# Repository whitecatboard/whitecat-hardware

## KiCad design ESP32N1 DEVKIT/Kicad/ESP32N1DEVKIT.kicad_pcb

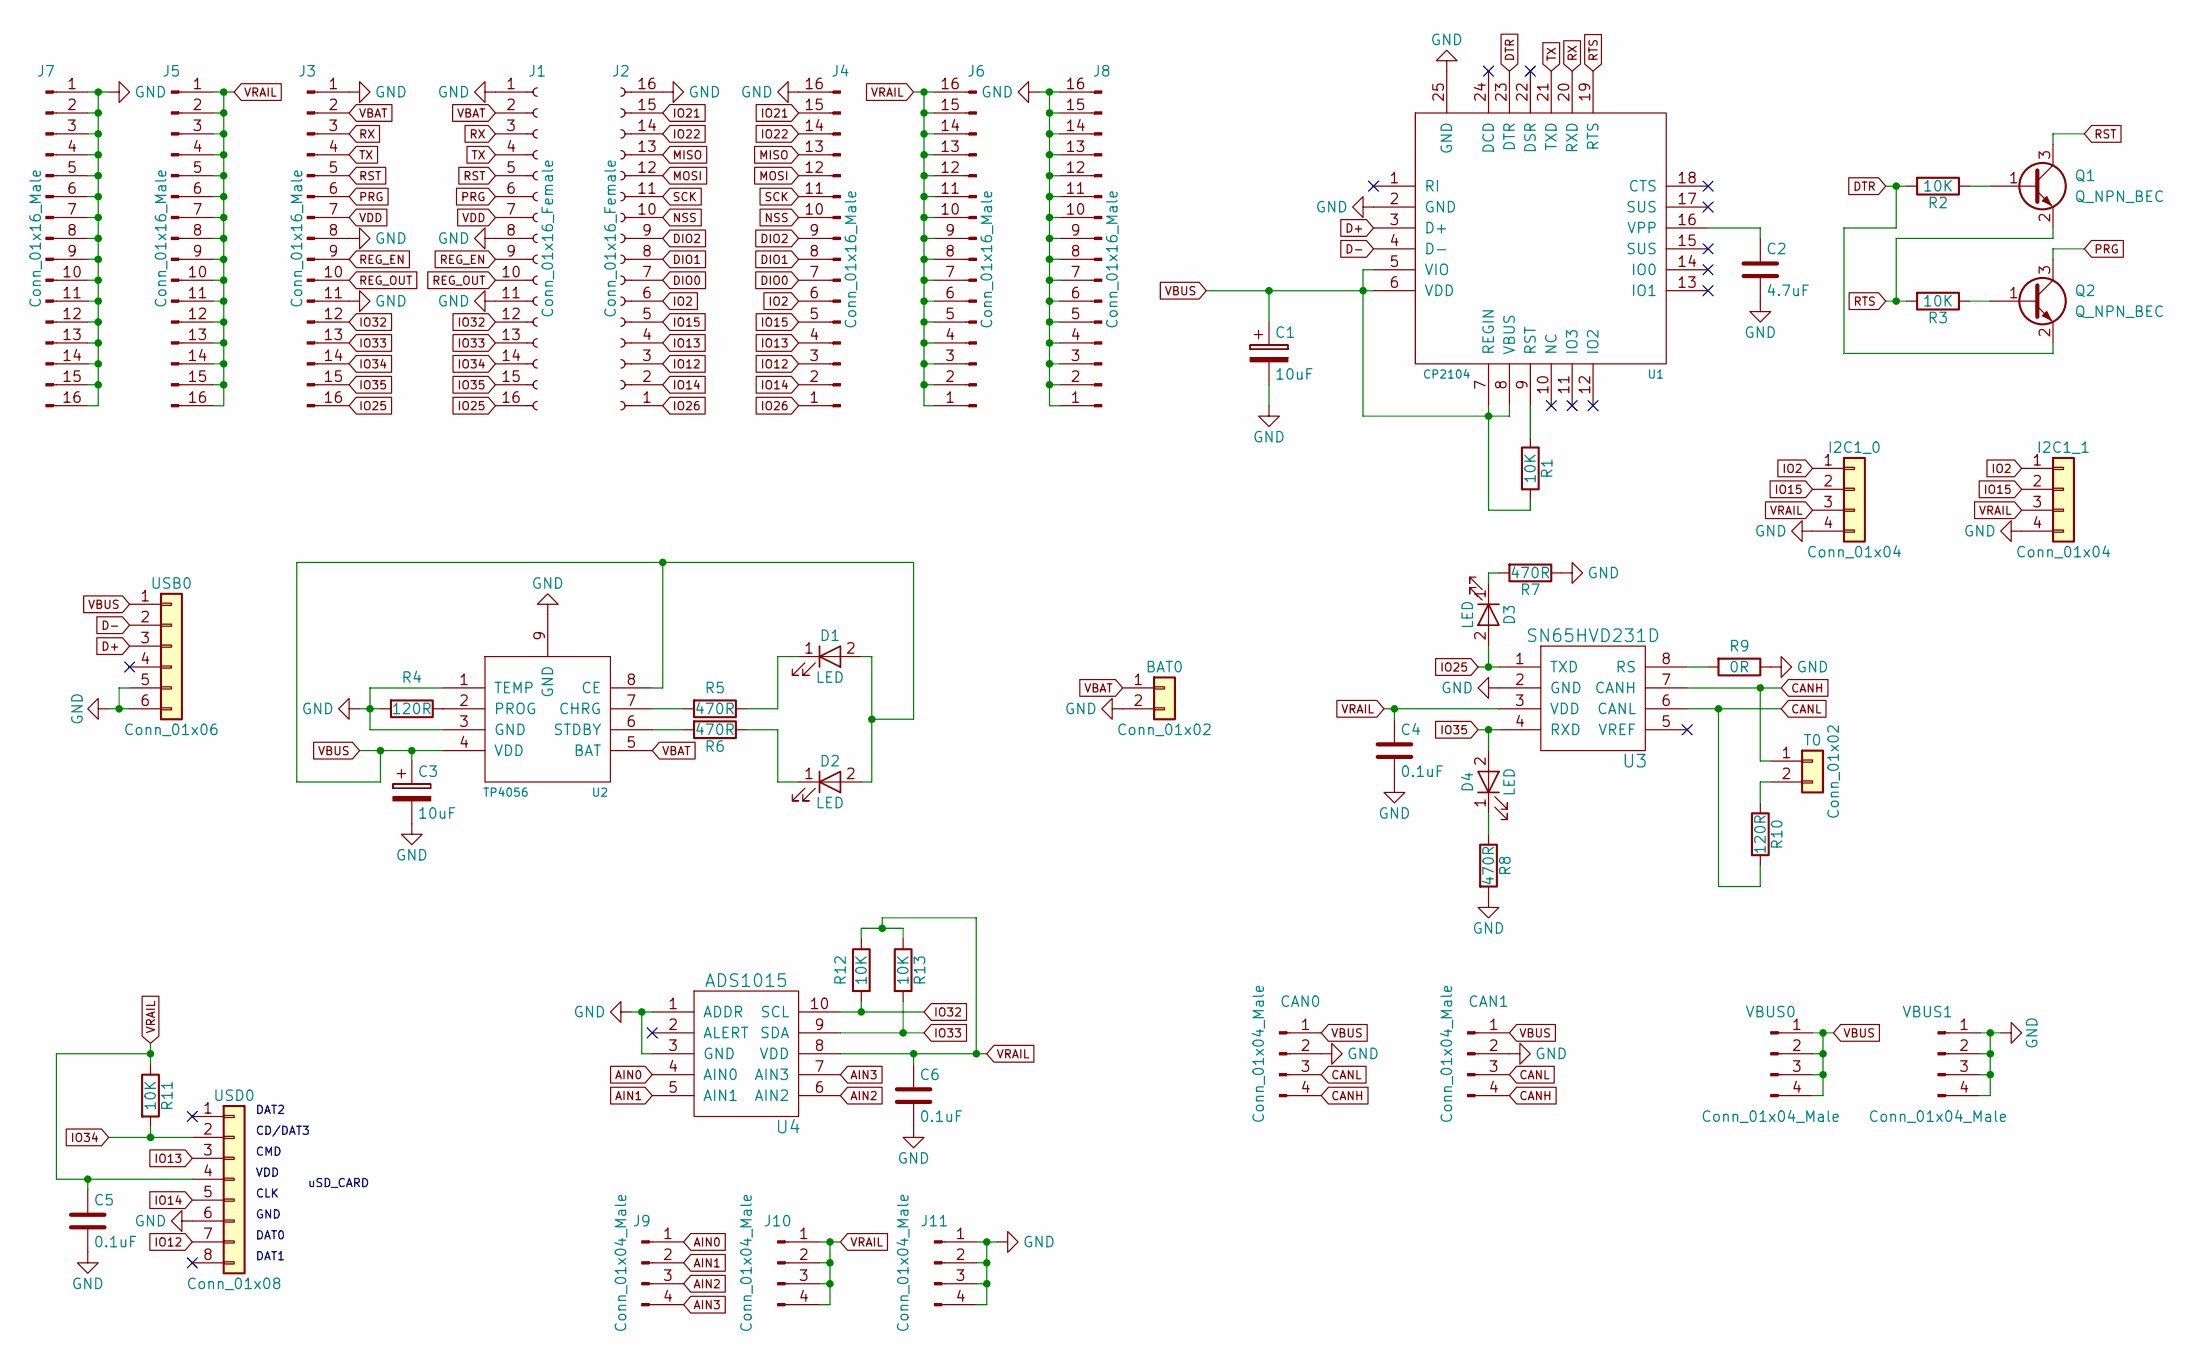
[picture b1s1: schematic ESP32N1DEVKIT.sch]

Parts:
BAT0: Conn_01x02; 18650_holder
C1, C3: 10uF; CP_Tantalum_Case-A_EIA-3216-18_Reflow
C2: 4.7uF; C_0603
C4, C5, C6: 0.1uF; C_0603
CAN0, CAN1: Conn_01x04_Male; micro_match_4p
D1, D2, D3, D4: LED; LED_0603
I2C1_0, I2C1_1: Conn_01x04; Pin_Header_Straight_1x04_Pitch2.54mm
J1, J2: Conn_01x16_Female; Pin_Header_Straight_1x16_Pitch2.54mm
J3, J4, J5, J6, J7, J8: Conn_01x16_Male; Pin_Header_Straight_1x16_Pitch2.54mm
J9, J10, J11: Conn_01x04_Male; Pin_Header_Straight_1x04_Pitch2.54mm
Q1, Q2: Q_NPN_BEC; SOT-23
R1, R2, R3, R11, R12, R13: 10K; R_0603
R4, R10: 120R; R_0603
R5, R6, R7, R8: 470R; R_0603
R9: 0R; R_0603
T0: Conn_01x02; Pin_Header_Straight_1x02_Pitch2.54mm
U1: CP2104; QFN-24-1EP_4x4mm_Pitch0.5mm
U2: TP4056; SOIC-8-1EP_3.9x4.9mm_Pitch1.27mm
U3: SN65HVD231D; SOIC-8_3.9x4.9mm_Pitch1.27mm
U4: ADS1015; TSSOP-10_3x3mm_Pitch0.5mm
USB0: Conn_01x06; USB_Mini-B
USD0: Conn_01x08; msd_socket
VBUS0, VBUS1: Conn_01x04_Male; Pin_Header_Straight_1x04_Pitch2.54mm

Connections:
AIN0: J9.1, U4.4 (AIN0)
AIN1: J9.2, U4.5 (AIN1)
AIN2: J9.3, U4.6 (AIN2)
AIN3: J9.4, U4.7 (AIN3)
CANH: CAN0.4, CAN1.4, T0.1, U3.7 (CANH)
CANL: CAN0.3, CAN1.3, R10.2, U3.6 (CANL)
D+: U1.3 (D+), USB0.3
D-: U1.4 (D-), USB0.2
DIO0: J2.7, J4.7
DIO1: J2.8, J4.8
DIO2: J2.9, J4.9
DTR: Q2.2 (E), R2.2, U1.23 (DTR)
GND: BAT0.2, C1.2, C2.2, C3.2, C4.2, C5.2, C6.2, CAN0.2, CAN1.2, I2C1_0.4, I2C1_1.4, J1.1, J1.8, J1.11, J2.16, J3.1, J3.8, J3.11, J4.16, J7.1, J7.2, J7.3, J7.4, J7.5, J7.6, J7.7, J7.8, J7.9, J7.10, J7.11, J7.12, J7.13, J7.14, J7.15, J7.16, J8.1, J8.2, J8.3, J8.4, J8.5, J8.6, J8.7, J8.8, J8.9, J8.10, J8.11, J8.12, J8.13, J8.14, J8.15, J8.16, J11.1, J11.2, J11.3, J11.4, R4.2, R7.1, R8.2, R9.1, U1.2 (GND), U1.25 (GND), U2.1 (TEMP), U2.3 (GND), U2.9 (GND), U3.2 (GND), U4.1 (ADDR), U4.3 (GND), USB0.5, USB0.6, USD0.6, VBUS1.1, VBUS1.2, VBUS1.3, VBUS1.4
IO2: I2C1_0.1, I2C1_1.1, J2.6, J4.6
IO12: J2.3, J4.3, USD0.7
IO13: J2.4, J4.4, USD0.3
IO14: J2.2, J4.2, USD0.5
IO15: I2C1_0.2, I2C1_1.2, J2.5, J4.5
IO21: J2.15, J4.15
IO22: J2.14, J4.14
IO25: D3.2 (A), J1.16, J3.16, U3.1 (TXD)
IO26: J2.1, J4.1
IO32: J1.12, J3.12, R12.2, U4.10 (SCL)
IO33: J1.13, J3.13, R13.2, U4.9 (SDA)
IO34: J1.14, J3.14, R11.2, USD0.2
IO35: D4.2 (A), J1.15, J3.15, U3.4 (RXD)
MISO: J2.13, J4.13
MOSI: J2.12, J4.12
NSS: J2.10, J4.10
unnamed: C2.1, U1.16 (VPP)
unnamed: D1.1 (K), R5.1
unnamed: D2.1 (K), R6.1
unnamed: D3.1 (K), R7.2
unnamed: D4.1 (K), R8.1
unnamed: Q1.1 (B), R2.1
unnamed: Q2.1 (B), R3.1
unnamed: R1.1, U1.9 (RST)
unnamed: R4.1, U2.2 (PROG)
unnamed: R5.2, U2.7 (CHRG)
unnamed: R6.2, U2.6 (STDBY)
unnamed: R9.2, U3.8 (RS)
unnamed: R10.1, T0.2
PRG: J1.6, J3.6, Q2.3 (C)
REG_EN: J1.9, J3.9
REG_OUT: J1.10, J3.10
RST: J1.5, J3.5, Q1.3 (C)
RTS: Q1.2 (E), R3.2, U1.19 (RTS)
RX: J1.3, J3.3, U1.20 (RXD)
SCK: J2.11, J4.11
TX: J1.4, J3.4, U1.21 (TXD)
VBAT: BAT0.1, J1.2, J3.2, U2.5 (BAT)
VBUS: C1.1, C3.1, CAN0.1, CAN1.1, D1.2 (A), D2.2 (A), R1.2, U1.5 (VIO), U1.6 (VDD), U1.7 (REGIN), U1.8 (VBUS), U2.4 (VDD), U2.8 (CE), USB0.1, VBUS0.1, VBUS0.2, VBUS0.3, VBUS0.4
VDD: J1.7, J3.7
VRAIL: C4.1, C5.1, C6.1, I2C1_0.3, I2C1_1.3, J5.1, J5.2, J5.3, J5.4, J5.5, J5.6, J5.7, J5.8, J5.9, J5.10, J5.11, J5.12, J5.13, J5.14, J5.15, J5.16, J6.1, J6.2, J6.3, J6.4, J6.5, J6.6, J6.7, J6.8, J6.9, J6.10, J6.11, J6.12, J6.13, J6.14, J6.15, J6.16, J10.1, J10.2, J10.3, J10.4, R11.1, R12.1, R13.1, U3.3 (VDD), U4.8 (VDD), USD0.4

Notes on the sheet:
DAT2
CD/DAT3
CMD
VDD
CLK
GND
DAT0
DAT1
uSD_CARD

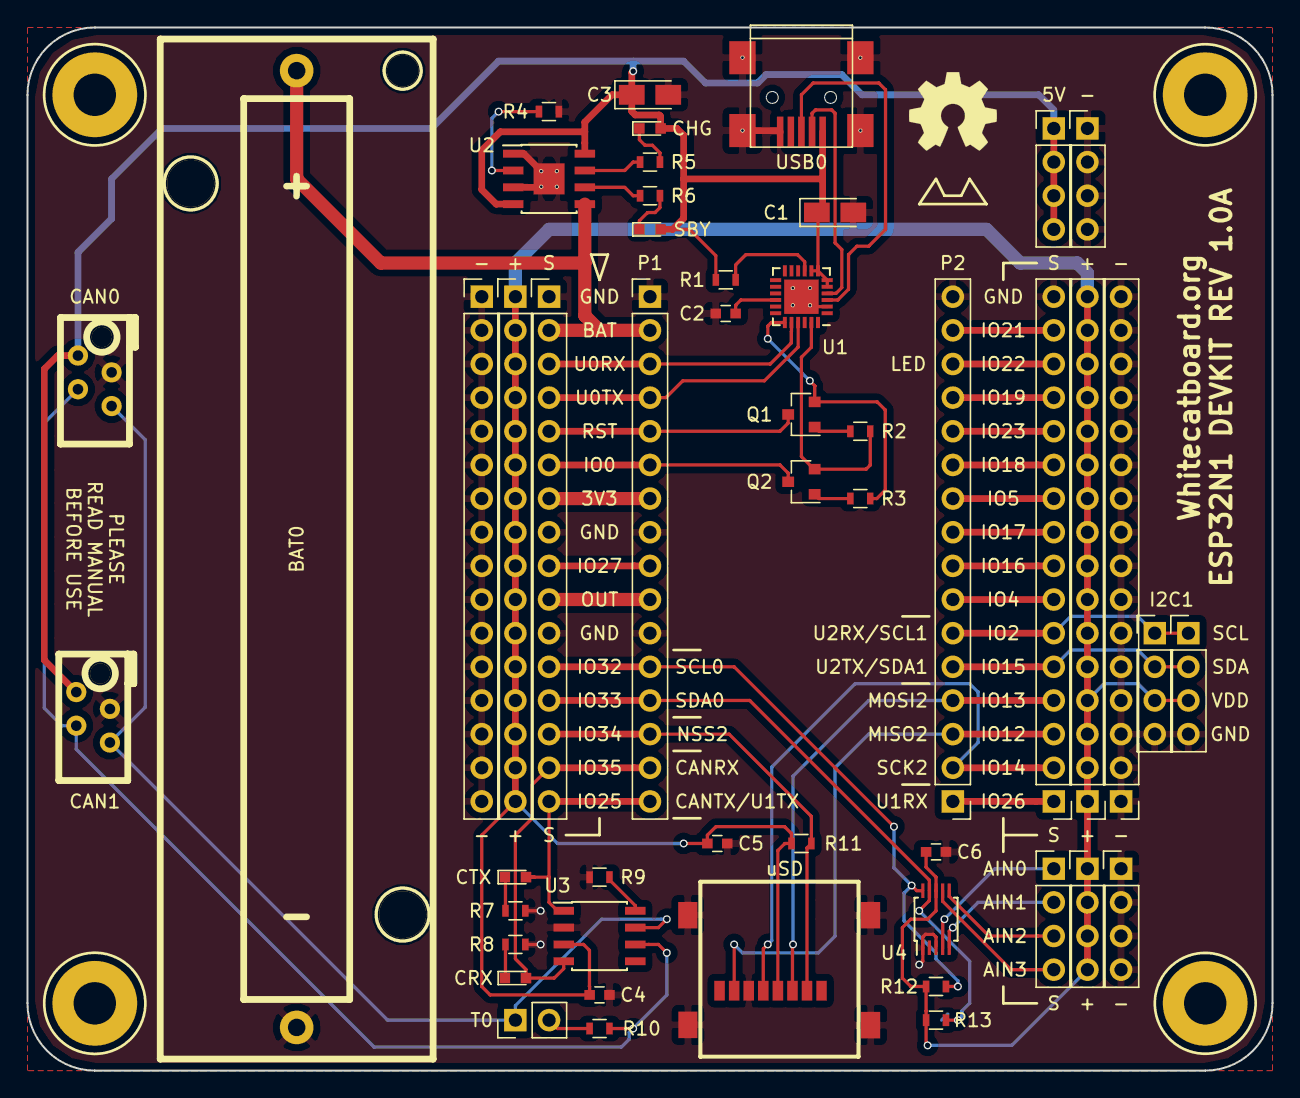
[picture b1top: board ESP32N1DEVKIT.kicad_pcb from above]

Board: 2 copper layers, 94.0 x 78.7 mm, 50 parts (0 on the bottom side), 54 nets.

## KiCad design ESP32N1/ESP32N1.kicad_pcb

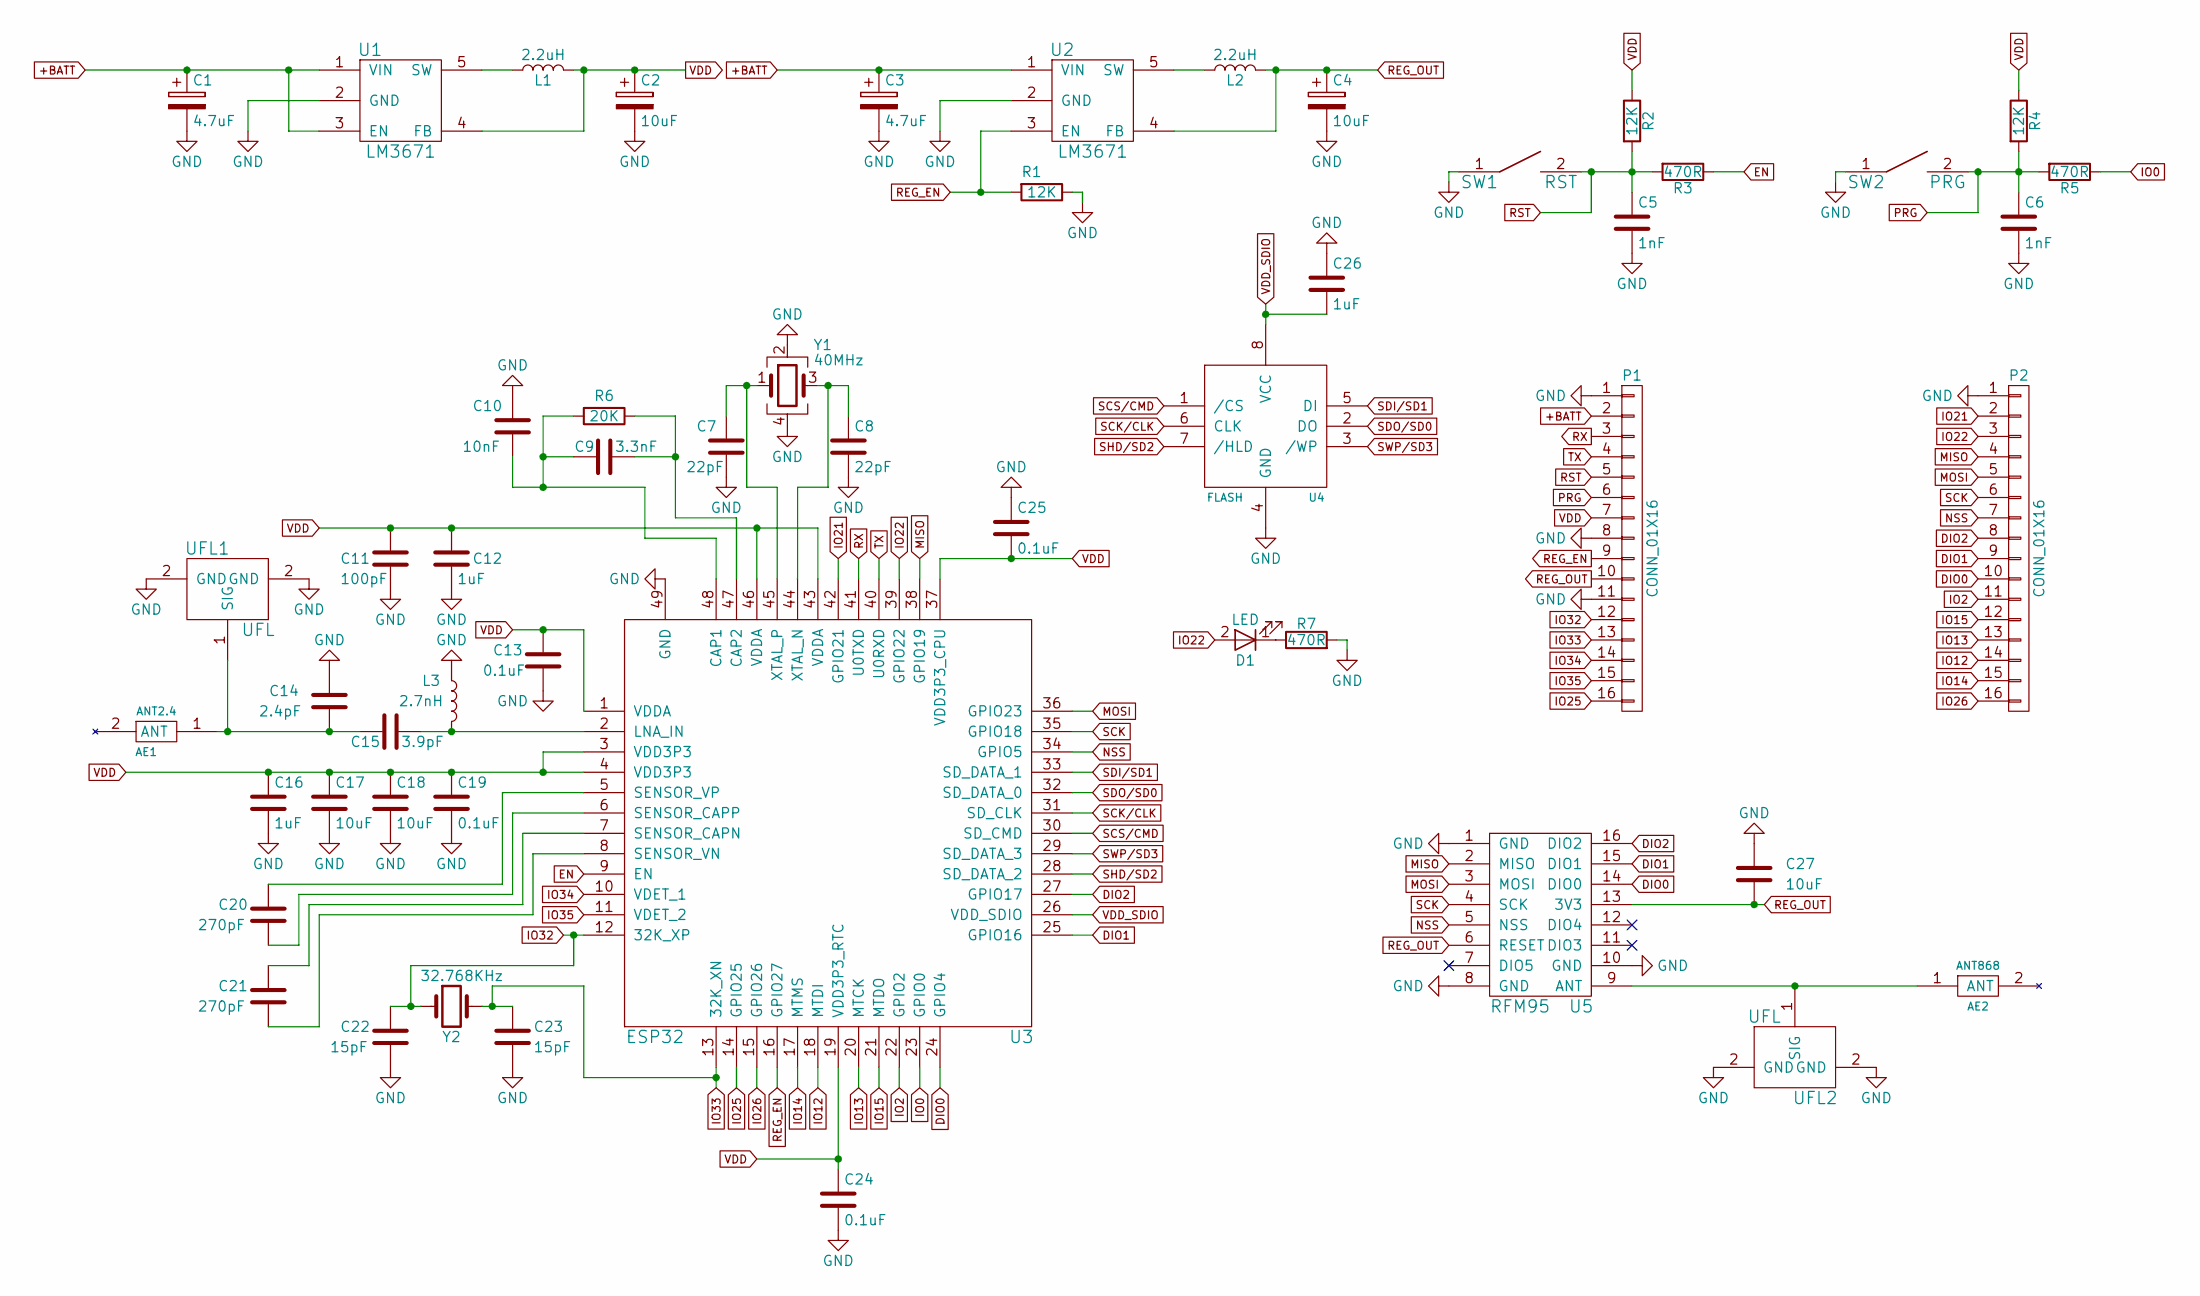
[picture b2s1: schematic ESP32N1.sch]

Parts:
AE1: ANT2.4
AE2: ANT868
C1, C3: 4.7uF; CP_Tantalum_Case-A_EIA-3216-18_Reflow
C2, C4: 10uF; CP_Tantalum_Case-A_EIA-3216-18_Reflow
C5, C6: 1nF; C_0603
C7, C8: 22pF; C_0603
C9: 3.3nF; C_0603
C10: 10nF; C_0603
C11: 100pF; C_0603
C12, C16, C26: 1uF; C_0603
C13, C19, C24, C25: 0.1uF; C_0603
C14: 2.4pF; C_0603
C15: 3.9pF; C_0603
C17, C18, C27: 10uF; C_0603
C20, C21: 270pF; C_0603
C22, C23: 15pF; C_0603
D1: LED; LED_0603
L1, L2: 2.2uH; R_0603
L3: 2.7nH; R_0603
P1, P2: CONN_01X16; Pin_Header_Straight_1x16_Pitch2.54mm
R1, R2, R4: 12K; R_0603
R3, R5, R7: 470R; R_0603
R6: 20K; R_0603
SW1: RST; PTS820
SW2: PRG; PTS820
U1, U2: LM3671; SOT-23-5
U3: ESP32; UQFN-48-1EP_6x6mm_Pitch0.4mm
U4: FLASH; SOIC-8-208
U5: RFM95; RFM95W
UFL1, UFL2: UFL; COAXIAL_U.FL-R-SMT-1
Y1: 40MHz; Crystal_SMD_TXC_7M-4pin_3.2x2.5mm
Y2: 32.768KHz; Crystal_SMD_MicroCrystal_CC7V-T1A-2pin_3.2x1.5mm

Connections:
+BATT: C1.1, C3.1, P1.2, U1.1 (VIN), U1.3 (EN), U2.1 (VIN)
DIO0: P2.10, U3.24 (GPIO4), U5.14 (DIO0)
DIO1: P2.9, U3.25 (GPIO16), U5.15 (DIO1)
DIO2: P2.8, U3.27 (GPIO17), U5.16 (DIO2)
EN: R3.1, U3.9 (EN)
GND: C1.2, C2.2, C3.2, C4.2, C5.2, C6.2, C7.2, C8.2, C10.1, C11.2, C12.2, C13.2, C14.1, C16.2, C17.2, C18.2, C19.2, C22.2, C23.2, C24.2, C25.1, C26.1, C27.1, L3.1, P1.1, P1.8, P1.11, P2.1, R1.1, R7.2, SW1.1, SW2.1, U1.2 (GND), U2.2 (GND), U3.49 (GND), U4.4 (GND), U5.1 (GND), U5.8 (GND), U5.10 (GND), UFL1.2 (GND), UFL2.2 (GND), Y1.2, Y1.4
IO0: R5.1, U3.23 (GPIO0)
IO2: P2.11, U3.22 (GPIO2)
IO12: P2.14, U3.18 (MTDI)
IO13: P2.13, U3.20 (MTCK)
IO14: P2.15, U3.17 (MTMS)
IO15: P2.12, U3.21 (MTDO)
IO21: P2.2, U3.42 (GPIO21)
IO22: D1.2 (A), P2.3, U3.39 (GPIO22)
IO25: P1.16, U3.14 (GPIO25)
IO26: P2.16, U3.15 (GPIO26)
IO32: C22.1, P1.12, U3.12 (32K_XP), Y2.1
IO33: C23.1, P1.13, U3.13 (32K_XN), Y2.2
IO34: P1.14, U3.10 (VDET_1)
IO35: P1.15, U3.11 (VDET_2)
MISO: P2.4, U3.38 (GPIO19), U5.2 (MISO)
MOSI: P2.5, U3.36 (GPIO23), U5.3 (MOSI)
NSS: P2.7, U3.34 (GPIO5), U5.5 (NSS)
unnamed: AE1.1 (ANT), C14.2, C15.2, UFL1.1 (SIG)
unnamed: AE2.1 (ANT), U5.9 (ANT), UFL2.1 (SIG)
unnamed: C7.1, U3.45 (XTAL_P), Y1.1
unnamed: C8.1, U3.44 (XTAL_N), Y1.3
unnamed: C9.1, R6.1, U3.47 (CAP2)
unnamed: C9.2, C10.2, R6.2, U3.48 (CAP1)
unnamed: C15.1, L3.2, U3.2 (LNA_IN)
unnamed: C20.1, U3.5 (SENSOR_VP)
unnamed: C20.2, U3.6 (SENSOR_CAPP)
unnamed: C21.1, U3.7 (SENSOR_CAPN)
unnamed: C21.2, U3.8 (SENSOR_VN)
unnamed: D1.1 (K), R7.1
unnamed: L1.1, U1.5 (SW)
unnamed: L2.1, U2.5 (SW)
PRG: C6.1, P1.6, R4.2, R5.2, SW2.2
REG_EN: P1.9, R1.2, U2.3 (EN), U3.16 (GPIO27)
REG_OUT: C4.1, C27.2, L2.2, P1.10, U2.4 (FB), U5.6 (RESET), U5.13 (3V3)
RST: C5.1, P1.5, R2.2, R3.2, SW1.2
RX: P1.3, U3.41 (U0TXD)
SCK: P2.6, U3.35 (GPIO18), U5.4 (SCK)
SCK/CLK: U3.31 (SD_CLK), U4.6 (CLK)
SCS/CMD: U3.30 (SD_CMD), U4.1 (/CS)
SDI/SD1: U3.33 (SD_DATA_1), U4.5 (DI)
SDO/SD0: U3.32 (SD_DATA_0), U4.2 (DO)
SHD/SD2: U3.28 (SD_DATA_2), U4.7 (/HLD)
SWP/SD3: U3.29 (SD_DATA_3), U4.3 (/WP)
TX: P1.4, U3.40 (U0RXD)
VDD: C2.1, C11.1, C12.1, C13.1, C16.1, C17.1, C18.1, C19.1, C24.1, C25.2, L1.2, P1.7, R2.1, R4.1, U1.4 (FB), U3.1 (VDDA), U3.3 (VDD3P3), U3.4 (VDD3P3), U3.19 (VDD3P3_RTC), U3.37 (VDD3P3_CPU), U3.43 (VDDA), U3.46 (VDDA)
VDD_SDIO: C26.2, U3.26 (VDD_SDIO), U4.8 (VCC)

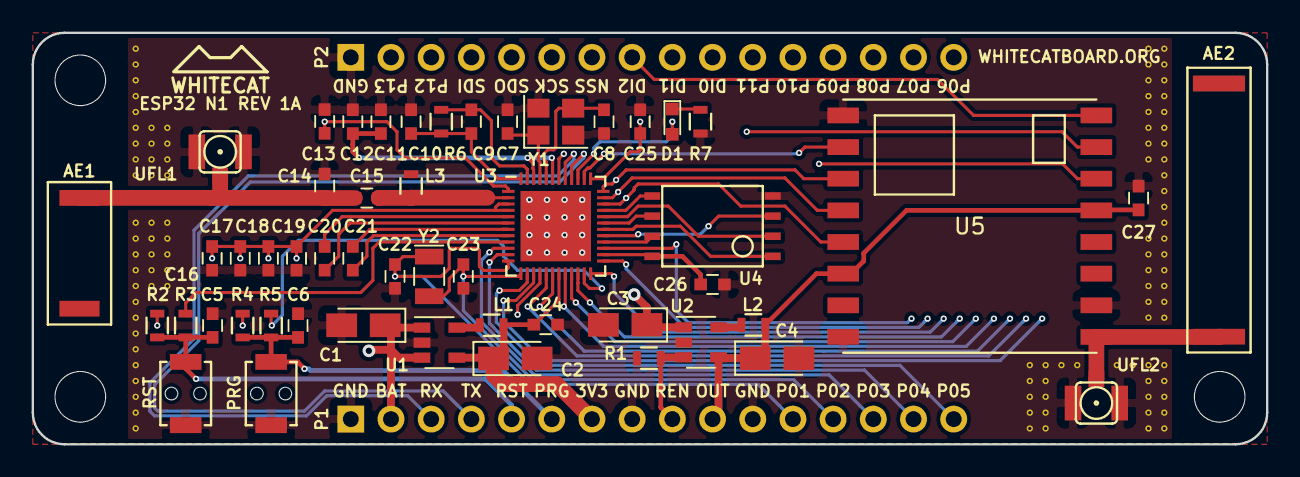
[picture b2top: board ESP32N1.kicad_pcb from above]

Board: 4 copper layers, 78.0 x 26.0 mm, 53 parts (0 on the bottom side), 52 nets.

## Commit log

2017-11-29 Added Kicad files for ESP32N1 DEVKIT board
2017-11-29 Added Kicad files for ESP32N1 board
2017-12-11 Added ESP32N1 DEVKI manual (spanish)
2018-02-22 Upgraded N1 DEVKIT manual
